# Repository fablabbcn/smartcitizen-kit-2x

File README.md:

# Smart Citizen Kit 2.X

Welcome to the Smart Citizen Kit main repository. Here you will find the hardware design files and the firmware for the SCK 2.1, SCK 2.2 and SCK 2.3 versions. [Click here for version 2.0](https://github.com/fablabbcn/smartcitizen-kit-20)

## Documentation

* If you want to read more about the Smart Citizen Kit or its sensors please check our [documentation](http://docs.smartcitizen.me/)
* If you just want to **upgrade** your Smart Citizen kit **firmware** please refer to the [Upgrading the Smart Citizen Kit Firmware](https://docs.smartcitizen.me/guides/firmware/upgrading-the-firmware/) guide.
* If you want to change something and build the firmware, use the [Building and flashing the Smart Citizen Kit firmware](https://docs.smartcitizen.me/guides/firmware/edit-the-firmware/) guide.
* The SCK provides a comprehensive command shell over USB to manage all the kits functionalities for advanced users: [Using the Smartcitizen Kit shell](https://docs.smartcitizen.me/guides/getting-started/using-the-shell/) guide.
* A compilation of Smartcitizen hardware work in a single **open publication:** [_Hardware X: Special Issue on Open-Hardware for Environmental Sensing and Instruments_](https://doi.org/10.1016/j.ohx.2019.e00070).
* You can also follow the [forum](https://forum.smartcitizen.me/) for updates and ask questions there for support.

## Development

In this repository you can find:

* The Smart Citizen Kit hardware [design files](./hardware).
* The [bootloader](./bootloader) and [main firmware](./sam) (C++) for the SAMD21 microcontroller.
* The [main firmware](./esp) for the ESP8266 microcontroller.
* A [mobile web UI](./mock-api) for setting up the kit.

## Related Smart Citizen repositories

* Platform Core API [github.com/fablabbcn/smartcitizen-api](https://github.com/fablabbcn/smartcitizen-api)
* Platform Web [github.com/fablabbcn/smartcitizen-web](https://github.com/fablabbcn/smartcitizen-web)
* Platform Onboarding [github.com/fablabbcn/smartcitizen-onboarding-app](https://github.com/fablabbcn/smartcitizen-onboarding-app)
* Kit Enclosures [github.com/fablabbcn/smartcitizen-enclosures](https://github.com/fablabbcn/smartcitizen-enclosures)
* Useful software resources for communities [github.com/fablabbcn/smartcitizen-toolkit](https://github.com/fablabbcn/smartcitizen-toolkit)
* Advanced data analysis tools [github.com/fablabbcn/smartcitizen-data](https://github.com/fablabbcn/smartcitizen-data)
* Python API connector [github.com/fablabbcn/smartcitizen-connector](https://github.com/fablabbcn/smartcitizen-connector)
* Analog Sensor Board [github.com/fablabbcn/smartcitizen-analog-sensor-board](https://github.com/fablabbcn/smartcitizen-analog-sensor-board)
* PM Board [github.com/fablabbcn/smartcitizen-kit-pm-board](https://github.com/fablabbcn/smartcitizen-kit-pm-board)

## License

All the software unless stated is released under [GNU GPL v3.0](https://github.com/fablabbcn/smartcitizen-kit-20/blob/master/LICENSE) and the hardware design files under [CERN OHL v1.2](https://github.com/fablabbcn/smartcitizen-kit-20/blob/master/hardware/LICENSE)

## Funding

This work has received funding from the European Union's Horizon 2020 research and innovation program under the grant agreement [No. 689954](https://cordis.europa.eu/project/rcn/202639_en.html)

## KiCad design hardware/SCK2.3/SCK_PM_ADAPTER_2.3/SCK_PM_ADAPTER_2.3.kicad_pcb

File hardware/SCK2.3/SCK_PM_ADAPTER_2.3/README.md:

# SCK 2.3 PM adapter (SEN5x / SEN6x)

Small board that replaces the Urban board and connects a Sensirion SEN5x or SEN6x to the SCK 2.3 Data board. KiCad 10 project.

- **J1**: 2x8 SMD male header, same footprint, position and pin numbering as the Urban board 2.3 `CONN_DATA` (bottom side).
- **J2**: JST GH 6 pin `SM06B-GHS-TB`, same footprint and position as the Urban board 2.3 `PM_SENSOR` (bottom side). The footprint is copied from the Eagle design because the KiCad library one is its mirror image, so the existing cables keep the same pinout.
- Same outline and holes as the Urban board 2.3, so it fits in the same place.

## Power

The PM connector on the Urban board gets 5 V from the Data board step-up (ETA1036-50, enabled by PA06 `pinPM_ENABLE`). The SEN6x needs 3.15–3.6 V (3.6 V absolute maximum), so it can't go on that line. Disabling the step-up doesn't help: its output is disconnected in shutdown, so the line goes to 0 V.

**JP1** selects the sensor supply. Set it before plugging in the sensor: 5 V destroys a SEN6x.

| JP1 | Supply | Sensor |
|-----|--------|--------|
| 1-2 | +5 V (step-up) | SEN5x (4.5–5.5 V) |
| 2-3 | 3V3 | SEN6x |

The 3V3 comes from one of two sources. Fit only one of them:

- **R1 (default): AP7361C-33E LDO from the switched 5 V.** The firmware can still power the sensor off with PA06, and the sensor is isolated from the Wi-Fi current bursts on the 3V3 rail. Dissipation is about 0.2 W at 110 mA.
- **R2 (not fitted): the Data board 3V3 rail (LD39200, 2 A, behind a 1.5 A fuse).** This has enough current for the SEN66's 350 mA peaks. However, the sensor is then always powered, and the rail is shared with the ESP8266. The SEN66 allows only 30 mV of supply ripple, so this option is there to measure whether the shared rail is clean enough.

I2C pull-ups (10k to 3V3) are on the Data board. The SEN6x and SEN5x I2C pins are 5 V tolerant.

## Firmware

There is no SEN6x support in the firmware yet. Without the Urban board, the Urban sensors are not detected and are skipped.

## Files

- `SCK_PM_ADAPTER_2.3.kicad_sch`, `.kicad_pcb`, `.kicad_pro`, `SCK_PM_ADAPTER.pretty/` (J2 footprint)
- `SCK_PM_ADAPTER_2.3.pdf`: schematic
- `SCK_PM_ADAPTER_2.3_PRODUCTION.zip`: gerbers, drill, BOM, positions

Status: v0.1, not manufactured or tested yet.

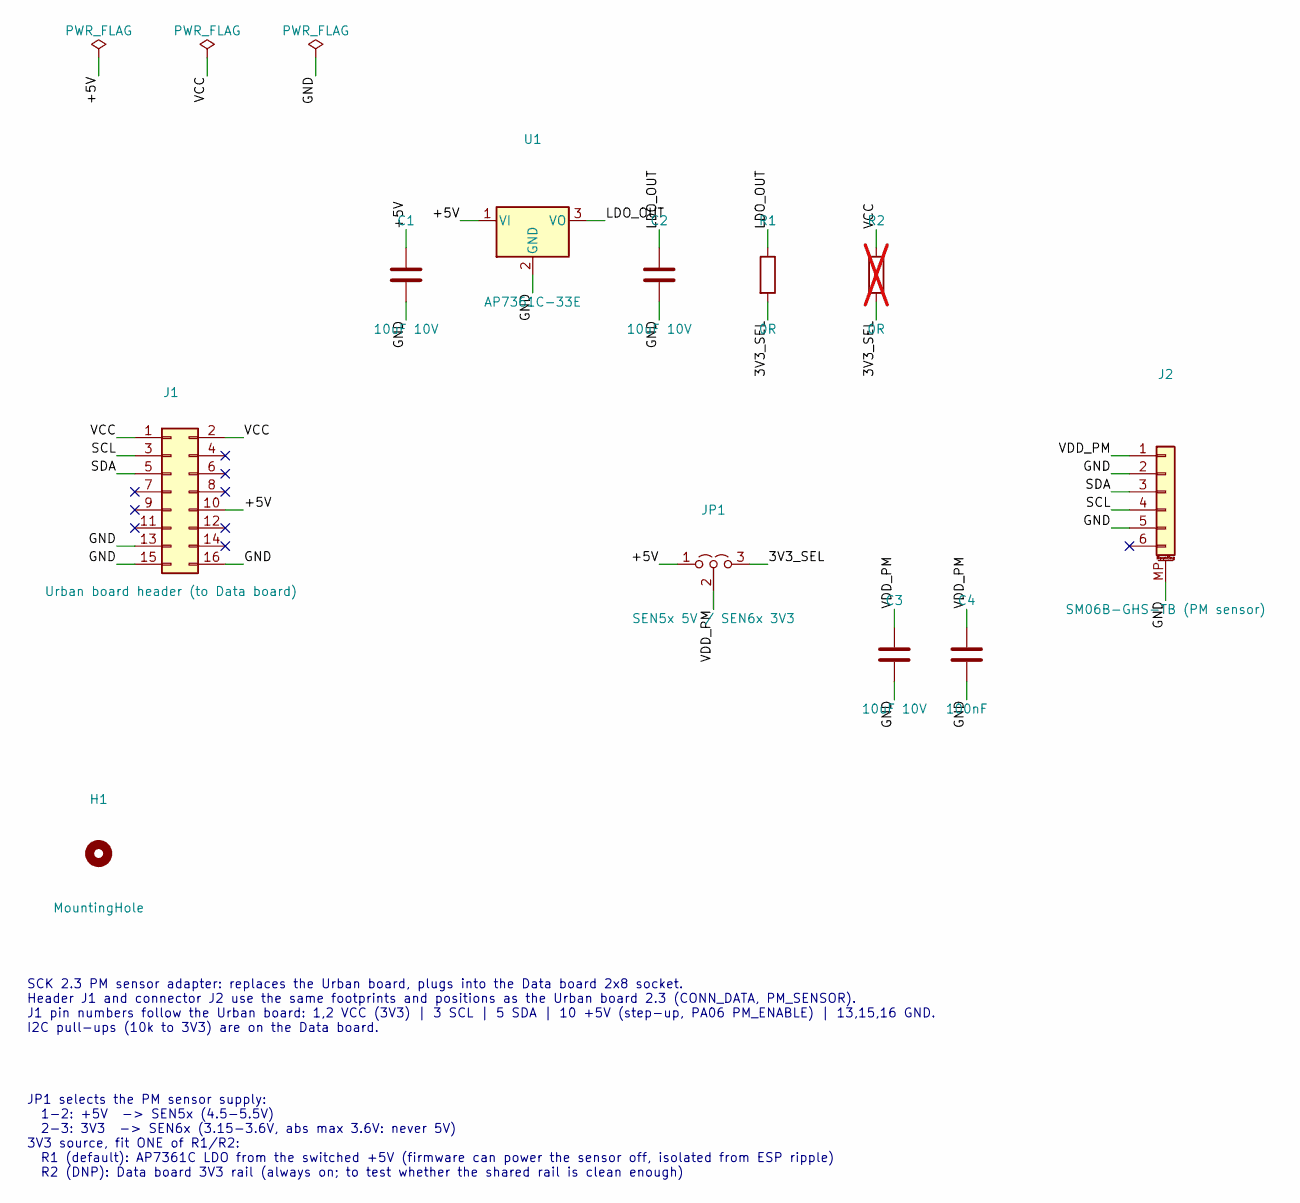
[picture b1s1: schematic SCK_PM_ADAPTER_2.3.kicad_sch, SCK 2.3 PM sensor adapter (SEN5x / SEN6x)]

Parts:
C1, C2, C3: 10uF 10V; C_0805_2012Metric
C4: 100nF; C_0603_1608Metric
H1: MountingHole; MountingHole_3.5mm
J1: Urban board header (to Data board); PinHeader_2x08_P2.54mm_Vertical_SMD
J2: SM06B-GHS-TB (PM sensor); SM06B-GHS-TB_SCK
JP1: SEN5x 5V / SEN6x 3V3; PinHeader_1x03_P2.54mm_Vertical
R1: 0R; R_0603_1608Metric
R2: 0R; R_0603_1608Metric; not fitted
U1: AP7361C-33E; SOT-223-3_TabPin2

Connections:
/3V3_SEL: JP1.3 (B), R1.2, R2.2
/+5V: C1.1, J1.10, JP1.1 (A), U1.1 (VI)
/GND: C1.2, C2.2, C3.2, C4.2, J1.13, J1.15, J1.16, J2.2, J2.5, J2.MP (MountPin), U1.2 (GND)
/LDO_OUT: C2.1, R1.1, U1.3 (VO)
/SCL: J1.3, J2.4
/SDA: J1.5, J2.3
/VCC: J1.1, J1.2, R2.1
/VDD_PM: C3.1, C4.1, J2.1, JP1.2 (C)

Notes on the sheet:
SCK 2.3 PM sensor adapter: replaces the Urban board, plugs into the Data board 2x8 socket. Header J1 and connector J2 use the same footprints and positions as the Urban board 2.3 (CONN_DATA, PM_SENSOR). J1 pin numbers follow the Urban board: 1,2 VCC (3V3) | 3 SCL | 5 SDA | 10 +5V (step-up, PA06 PM_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
JP1 selects the PM sensor supply: 1-2: +5V -> SEN5x (4.5-5.5V) 2-3: 3V3 -> SEN6x (3.15-3.6V, abs max 3.6V: never 5V) 3V3 source, fit ONE of R1/R2: R1 (default): AP7361C LDO from the switched +5V (firmware can power the sensor off, isolated from ESP ripple) R2 (DNP): Data board 3V3 rail (always on; 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

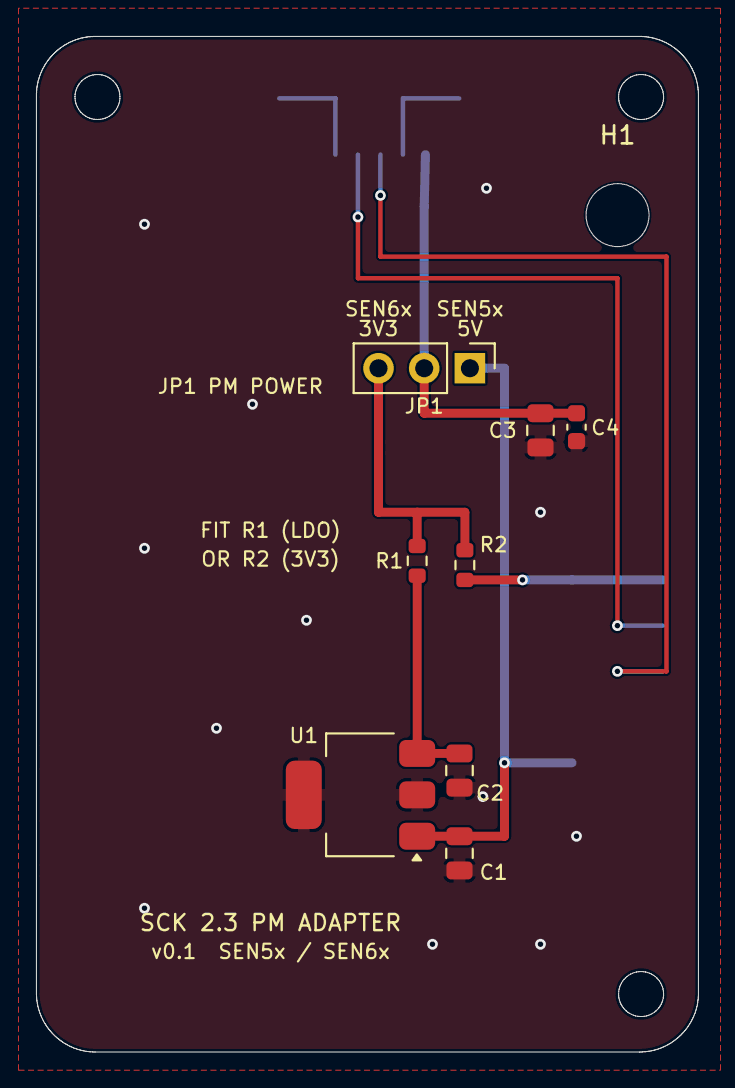
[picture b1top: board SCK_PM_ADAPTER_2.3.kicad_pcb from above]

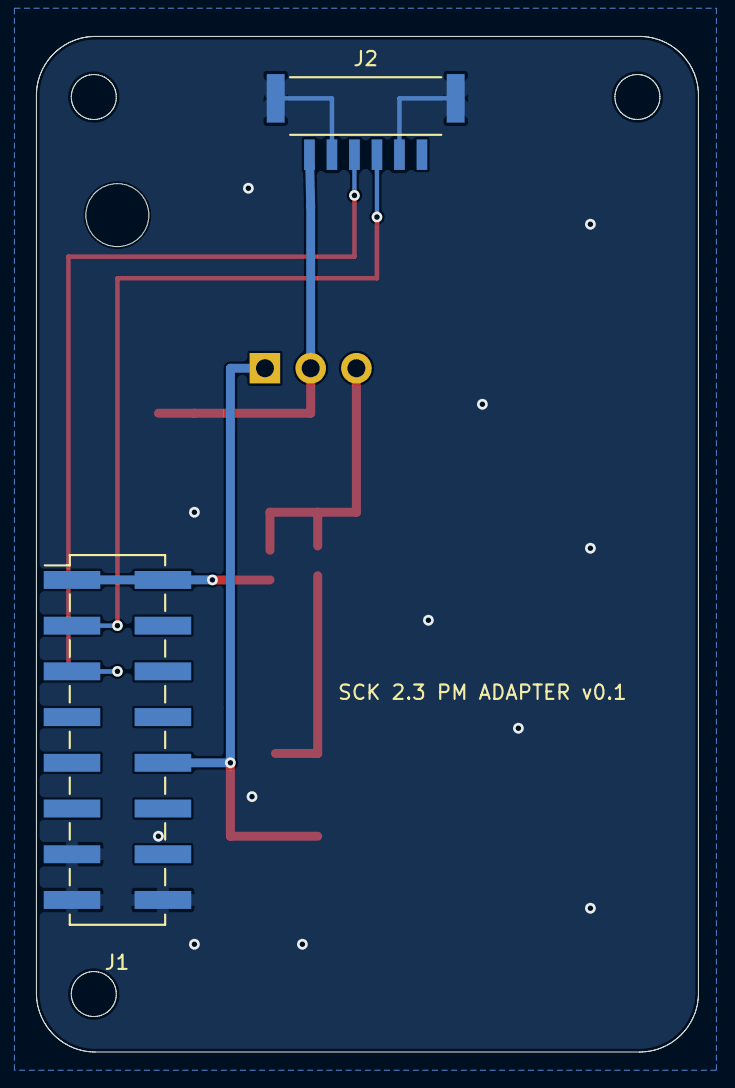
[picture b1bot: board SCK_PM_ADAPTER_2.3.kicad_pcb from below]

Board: 2 copper layers, 36.8 x 56.4 mm, 11 parts (2 on the bottom side), 8 nets.

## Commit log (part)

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2023-04-18 Side by side buttons in esp setup
2023-04-18 Upgrade deprecated gulp modules names
2023-05-11 Fix Atlas EC not receiving all data on very long readings
2023-05-11 Fix Atlas temperature compensation not using DS18B20 sensor
2023-05-16 Add PMS5003 PN Count IDs
2023-05-18 Implemented initial support for SPS30
2023-05-18 Urban code cleanUp
2023-05-18 Improved Urban board startup
2023-05-18 Fix startup hang on External SHT Temp/Hum sensor
2023-05-23 SPS30 Fixes and improvements
2023-05-23 SPS30 sleep function is n ow public (missing in last commit)
2023-05-23 Initial SEN5X implementation
2023-05-23 Don't print error message when urban board sensors are not detected
2023-05-23 Fix PM not sending proper sensor state after urgan getReading() refactor
2023-05-23 Retab and cleanUp
2023-05-23 Added platform Id's to SEN5X metrics
2023-05-23 Fix on Sensirion lib not detecting SAMD I2C size
2023-05-23 Fix detection for SEN5X models
2023-05-23 First iteration of full metric support on SEN54 and SEN55
2023-05-30 Implemented auxiliary SFA30 Formaldehyde Sensor Module
2023-06-01 Updated gitignore
2023-06-02 Added SFA30 platfor id's and fixed some start issues on the same sensor.
2023-06-08 Implemented SEN5X without any external dependency
2023-06-08 Really merge SEN5X new code
2023-06-12 Added defines to disable sensors on build to save RAM
2023-06-13 Avoid SEN5X to trigger cleaning after new firmware upload.
2023-06-15 SPS30 manage celan interval, some touches to SEN5X and SPS30
2023-06-16 Improved RAM management
2023-06-16 Hardware info now contains last reset cause
2023-06-22 Implemented RSSI WiFi signal as a sensor
2023-06-26 Cleaned up make.py help message
2023-07-05 Updated arduino core
2023-07-05 Updated tools submodule
2023-07-05 Hardware info now contains git branch, info file is now json format
2023-07-05 Updated platformio.ini lib_deps syntax
2023-07-06 Updated led code, brightness can be adjusted, breathing while booting to detect hangs
2023-07-06 Missing from led brightness commit
2023-07-06 SD card work: updated lib, file manager functions
2023-07-10 Sd card code refurbished, file manager functions working
2023-07-10 Fix led not updating on STATIC mode
2023-07-11 Moved BME68X to Urban Board Sensors
2023-07-11 BME68X details
2023-07-14 SEN5X sensor now saves VOCS state and restores it when needed
2023-07-17 Added platform ID to several sensors
2023-07-17 Removed sensor control property, wasn't used
2023-07-18 Removed Arduino String from sensor functions
2023-07-24 Add LPS33 Barometric pressure sensor
2023-07-31 AS7331 initial iplementation, still WIP
2023-07-31 Some touches to SEN5X
2023-10-19 ifdef disable CCS811 and comment on fix compiling
2023-10-19 SEN5X cleaning is not triggered if time is not set
2023-10-23 Save and restore VOC state correctly
2023-10-23 SEN5X monitor mode is now working properly
2023-10-23 Always publish to shell SEN5X model
2023-10-24 Finished AS7331 implementation
2023-10-24 Updated test protocol for SCK 2.2
2023-10-27 Add bugfix branch while sparkfun CCS811 PR is not merged
2023-10-27 Fix missing ifdef for SEN5X init
2023-10-30 Rename Sck_PM to Sck_PMS to avoid confusion
2023-10-30 Add ifdefs for pressure sensors and rename MPL
2023-10-30 Minor cosmetic change
2023-10-30 Minor cosmetic changes and trailspace cleanup
2023-10-30 Base configuration for TA
2023-10-30 Urban Sensors 2.2 and datasheet fix for LPS33
2023-11-06 Add build workflow
2023-11-06 Add submodules
2023-11-07 Enable automation in dev branch
2023-11-07 Update tools submodule
2023-11-07 Remove cached from platformio
2023-11-14 Change LPS Sensor name for consistency
2023-11-14 Finalise test protocol for SCK2.2
2023-11-17 Add variants to compiling process
2023-11-17 Change build process in workflow
2023-11-20 Check building process in various platforms.
2023-11-27 Fix missing csv speed file update to new sckfile model
2023-12-20 Default activated sensors per env
2023-12-20 Minor typo
2023-12-21 Hardware version now based on env define
2024-02-27 Sensirion libs are now fixed to last version
2024-02-27 SEN5X: VOC's and NOX's are now disabled by default
2024-02-27 SEN5X: New continous mode when VOC's or NOX's are enabled
2024-02-27 SEN5X: sensors are now automatically enabled/disabled and its interval changed in groups: PM, PN, TH, VOC and NOX
2024-02-27 SEN5X: if reading interval is smaller than warmUp continous mode is enabled
2024-02-29 Add option for compiling to .hex
2024-02-29 Add env for test firmware. Change define
2024-02-29 Minor fix on aux wire test firmware output
2024-02-29 Add hardware for SCK2.2
2024-03-01 Add the possibility to flash other bootloaders based on Makefile.user
2024-03-01 Update bootloader submodule
2024-03-05 Enforce reset after using shell mode to get a clean state
2024-03-05 Make ESP error visible to the user
2024-04-23 Minor fix in hardware Readme
2024-05-17 Only send compensation in atlas sensors when needed
2024-05-27 Add temperature and humidity corrections for all modes and depending on SCK21 or SCK22
2024-05-29 Improve corrections for temperature and relative humidity, also in sd card mode
2024-06-03 Improve T correction of 2.1
2024-06-06 Only send temperature command if temperature reading is valid
2024-07-24 Hardware files for SCK2.3 - WIP
2024-08-21 Bump sam and esp version to 0.9.9
2024-09-10 Add SCK2.3
2024-09-10 Reorganize hardware files and fix readme
2024-10-04 Atlas delay should be sufficient after transmission is ended to avoid non-ready data
2024-10-04 Add sleep wakeup to atlas drivers and avoid erroneous data on wake
2024-10-23 Expose STA MAC address along with softAP one
2024-10-28 Remove seeduino test plan
2024-10-28 Revert delay position. Increment to shortwait
2024-10-28 WIP tcomp command for atlas sensors
2024-10-28 Add commands to enable temperature compensation on atlas sensors
2024-11-08 Pio env now on info hash
2024-11-08 Revert "Enhancement/pio env info"
2024-11-20 Turn off all SEN5X metrics when button is down.
2024-11-20 Improve output of debug commands
2024-11-21 Fix ifdefs for external temperature sensor
2024-11-25 Minor fix on output of atlas control sensor command
2024-12-09 Bump to 0.9.10
2024-12-12 Update test plan and remove unused #define
2025-01-31 Improve make.py to avoid flashing when building firmware fails
2025-02-13 Minor fix on make.py
2025-03-25 Urban Board Silkscreen
2025-07-17 Update README.md
    Replacing the SCK welcome README with DaphiSensor README
2025-07-21 Remove ADS1X15 fork
    Remove the fork as adafruit has refurbished it and we do not need a fork for this anymore. They can now pass a Wire object to the begin.
2025-08-01 Create Hardware Overview
    Some important details about the hardware in use
2025-08-01 Add file extension to the file name
2025-08-01 Update Hardware Overview.md
    fix typos
2025-08-01 Update README.md
    updated with new links and information to guidelines and hardware overview
2025-08-07 Fix VOCstate buffer size bug and add model checks
    * Fixes size for VOC state accounting for CRC
    * Adds checks for model version clash
2025-08-10 Add .clang-format and .clang-tidy configuration files
2025-08-10 Add Docker setup and scripts for clang-tidy and clang-format checks
2025-08-11 Update README.md
    Changed references to the wiki
2025-08-11 Delete guides and manuals directory
    Content is now in the Wiki
2025-08-12 Add CI job for Clang format and tidy checks
2025-08-12 added .ino files to the checks
2025-08-12 test file to test autmoted checks
2025-08-12 Update clang check script paths in CI workflow and README
2025-08-12 Refactor clang checks to only format and analyze changed files
2025-08-12 Change submodule checkout to false in clang checks workflow
2025-08-12 test file to test the checks
2025-08-12 update git fetch command in CI workflow
2025-08-12 update clang-tidy command to treat warnings as errors
2025-08-12 removed tests.cpp for testing
2025-08-18 Update README.md
    Fixed broken links
2025-08-26 Typical particle size is not in #/cm3 - remove convertion
2025-09-03 Fix continuous mode readings
    If continuous mode is activated most SEN5X readings went wrong because
    the already read values weren't returned but get_reading() returned an
    error state. By checking if update() failed because of no new values
    available in continuous mode (SEN54 and SEN55) we can return the stored
    values safely.
2025-09-09 Only check pio environments when needed
2025-09-09 Add forced continuous mode to check
2025-09-09 Add forced continuous mode
2025-09-09 Test on SCK reboot for retrieving VOC state from sensor
2025-09-10 Move vocStateFromSensor and improve debug
2025-09-10 Minor improvements on debug
2025-09-10 Add valid flag and timestamp on VOCState function
2025-09-12 Attempt at making first VOC reading not reported
2025-09-12 Fix returned buffer on VOCstate as it doesn't include CRC
2025-09-16 Add RHT/Gas only mode to SEN55
2025-09-18 Upgrade ads1x15 library
2025-09-18 Add SHT31 in external sensor name to allow parsing of commands
2025-09-18 Minor comment
2025-09-18 Minor typo in units
2025-09-18 Fix humidity offset type
2025-09-18 Create interface for SHT31 custom calibration
2025-09-18 Adds rht calibration to external sensors
    * Minor fixes in WITH_RANGE define
    * Adds clear command to reset calibration to default
2025-09-18 Fix not taking oled defaults
2025-09-22 Minor fix for non urban setups
2025-09-23 Change default sensor enables for SEN54 and SEN55
2025-09-25 Change default sensor enables for SEN54 and SEN55 Bump SAM version
2025-10-12 Fix upload script for newer Python version
2025-10-12 Disable softAP during startup
    To avoid a default popup WiFi network during ESP startup we explicitly
    disable it as early as possible.
2025-10-14 Fix shell parameter parsing
    It doesn't make sense to parse more tokens if the current one fails.
    TODO: Word in input should match a complete word in title and not just a
    substring.
2025-11-27 Fix sensor name for AS7331 UVC in Sensors.h
2026-01-07 Remove screen flag from platformio.ini
2026-01-07 Fix links in readme
2026-05-11 Add defines on test firmware
2026-05-12 Fix URL formatting for Adafruit ADS1X15 library
2026-05-12 Update gitignore
2026-05-12 Add env variables for testing procedure
2026-05-12 Add .internal to gitignore
2026-05-12 Make.py more robust
2026-05-12 Add fake credentials for tests
2026-05-12 Stop tracking .seeed and .internal
2026-05-12 Add .seeed file with WiFi credentials
2026-05-12 Add internal configuration for WiFi credentials
2026-05-12 Remove files again
2026-05-12 Add defaults to test credentials on env.py
2026-05-12 Fix on env.py
2026-05-18 Upgrade espressiff platform
    * Provides access to retry functions and password error checking
2026-05-18 Add constants with SC_ and uppercase
2026-05-18 Always retry SC_MAX_WIFI_RETRIES on Wi-Fi connection attempts
2026-05-18 Make sure espON flag is true after booting ESP
2026-05-18 Add new case for password error on ESP
2026-05-18 Set AutoReconnect to true on ESP after trying connection
2026-05-18 Rename mqttHellow to mqttHello
2026-05-18 Fix typo detected by pral2a/Claudio on other PR
2026-05-18 Replace "!!!" on error logs. Make error logs consistent
2026-05-18 More error logs
2026-05-18 Make switch-case statement consistent with brackets
2026-05-18 Experimental: add yield() statements on potentially blocking NTP requests
2026-05-18 Coding style and linting changes
2026-05-18 Fix error reported by Claudio and pral2a
2026-05-21 Fix image link just for fun and enhance forum support information
    Updated image link and improved forum support text.
2026-05-21 Correct image syntax in README.md
    Fix image link formatting in README
2026-05-21 Update image in README with new version photo
2026-05-22 Add potential chanes commented, not showing improvement
